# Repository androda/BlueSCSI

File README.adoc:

# F4 BlueSCSI
:toc: macro

`F4 BlueSCSI`, ported by https://github.com/androda[androda], is a fork of `BlueSCSI` which targets the STM32F401 and STM32F411 microcontrollers.

toc::[]

### Lineage
F4 BlueSCSI, BlueSCSI, and ArdSCSino are hardware that reproduces SCSI devices (hard disks) with an STM32 Microcontroller.

`BlueSCSI` was created by https://github.com/erichelgeson[erichelgeson]

`ArdSCSino-stm32` was created by https://github.com/ztto/ArdSCSino-stm32[ztto], and is the STM32 version of `ArdSCSino`

`ArdSCSino` was created by https://twitter.com/h_koma2[Tambo (TNB Seisakusho)]

## Discussion
Join us in #bluescsi on https://discord.gg/GKcvtgU7P9[Discord].

## Compatibility and Performance
https://github.com/androda/F4_BlueSCSI/wiki/System-Compatibility-and-Performance[Compatibility and Performance]

## Assembly
Assembly instructions are generally found on my separate site, here: https://androda.work/kit-assembly/
These aren't really assembly instructions either, mostly pictures of the assembled design with tips on which way things should be facing.

## Usage
https://github.com/erichelgeson/BlueSCSI/wiki/Usage[Usage] is intended to be the same as the parent project and will be kept in sync until the blue pill module's flash is all used.  Then F4 will start to diverge.

### Termination
Termination enable / disable is handled differently per board style.  See the instructions for each PCB design.

## Firmware Updates
https://github.com/androda/F4_BlueSCSI/wiki/Flashing-Firmware-Updates[Flashing Firmware Updates]

## Troubleshooting
(to be completed, currently similar to the parent repo - but there are no jumpers on these dev modules.)
https://github.com/erichelgeson/BlueSCSI/wiki/Troubleshooting

## Hardware Versions
Generally speaking, hardware versions follow a naming scheme.

Variant.Maker.Style.Version

For example: {F4.TbA.D.V1}

This is an F4 model from Tech by Androda, D is for Desktop and V1 means first revision.

## Development (Advanced, annoying to set up)
https://github.com/androda/F4_BlueSCSI/tree/main/docs/Dev_Instructions[Dev Instructions]

## Notes

### Building the Code
- Build experience is unfortunately complex due to Maple's STM32F4 compatibility issues

### Making Gerbers for JLCPCB
https://support.jlcpcb.com/article/44-how-to-export-kicad-pcb-to-gerber-files

BlueSCSI(TM) - Eric Helgeson - All rights reserved. - Used with permission

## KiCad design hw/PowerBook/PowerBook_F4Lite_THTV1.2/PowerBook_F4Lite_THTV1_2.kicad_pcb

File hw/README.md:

# F4 and F4Lite Hardware License

* © 2021 - 2022 Tech by Androda, LLC
* All hardware design files, design artifacts, and in general all files provided in the hardware section (/hw/ and below) are licensed Attribution-NonCommercial-ShareAlike 4.0 International (CC BY-NC-SA 4.0)
* https://creativecommons.org/licenses/by-nc-sa/4.0/legalcode

These files are provided AS-IS with no warranty of any kind to the maximum extent allowed by law.

License Explanation:

Hardware:
This license means that you can have these designs produced by the PCB maker of your choice, for your own personal use.
You, the licensee, are not permitted to re-sell the PCBs which are produced using these design and production files.  They are not licensed for sale of any kind, regardless of whether you have 'spares' left over.  Selling them 'at cost' or 'below cost' is also a violation of the license, because those are sales too.

3D Printable Files:
This license allows you to print these printable files yourself, or have them printed for you, for your own personal use.  You, the licensee, are not permitted to re-sell the printed parts which are produced under this license.  They are not licensed for sale of any kind, regardless of whether you made (or had made) more than you needed.  A sale 'at cost' or 'below cost' is still a sale and is a license violation.

All other files:
Seriously, why would you try to sell these?

Alternate Licensing available:
If you would like to produce these hardware designs and printed parts for sale, you are encouraged to contact Tech by Androda, LLC to arrange alternate licensing.  https://androda.work/about/

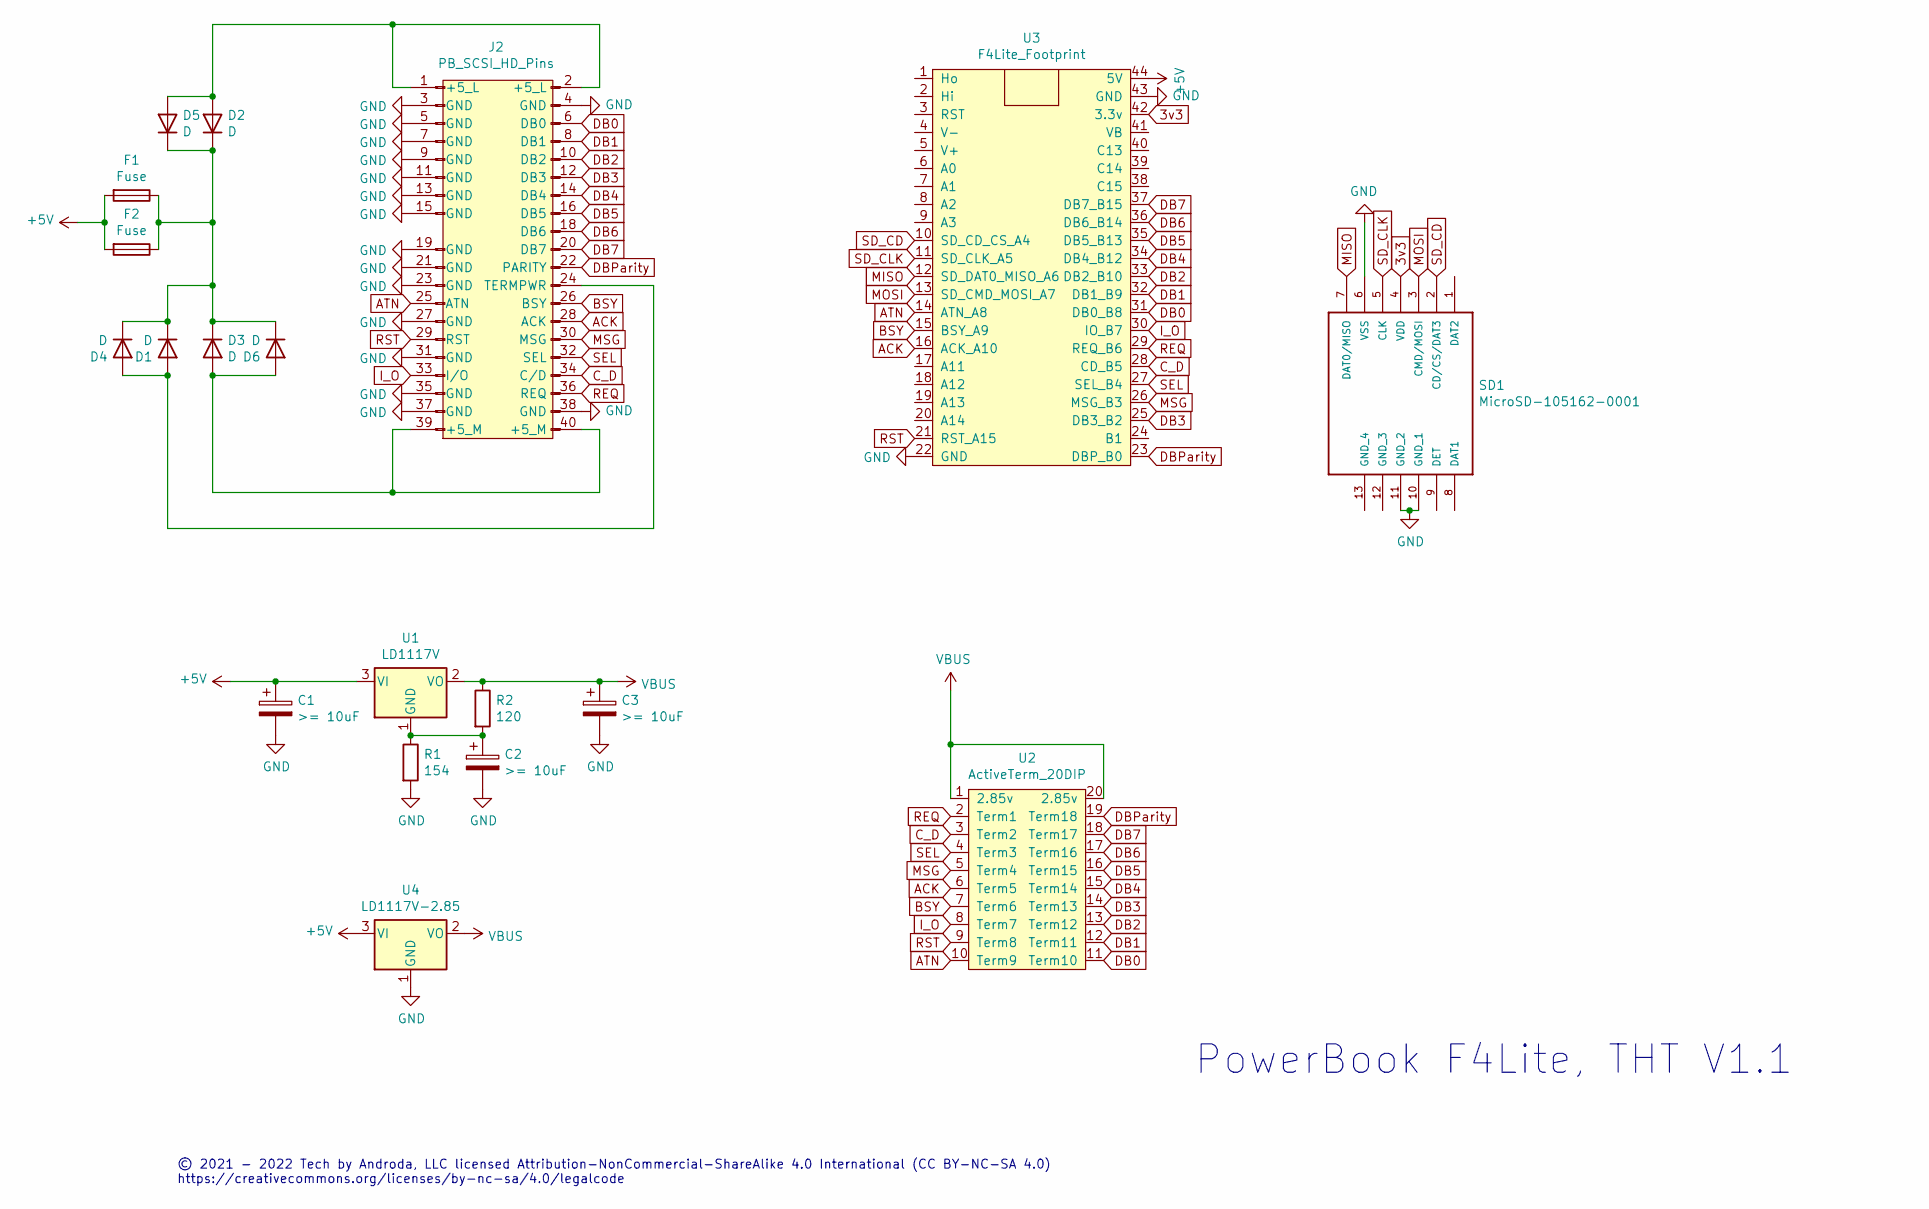
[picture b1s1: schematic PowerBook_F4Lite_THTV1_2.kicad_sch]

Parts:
C1, C2, C3: >= 10uF; C_1206_3216Metric_Pad1.42x1.75mm_HandSolder
D1, D2, D3: D; D_A-405_P10.16mm_Horizontal
D4, D5, D6: D; D_SMA
F1: Fuse; Fuse_BelFuse_0ZRE0005FF_L8.3mm_W3.8mm
F2: Fuse; Fuse_0805_2012Metric_Pad1.15x1.40mm_HandSolder
J2: PB_SCSI_HD_Pins; PowerBook_SCSI_40Pin_UpsideDown
R1: 154; R_Axial_DIN0204_L3.6mm_D1.6mm_P7.62mm_Horizontal
R2: 120; R_Axial_DIN0204_L3.6mm_D1.6mm_P5.08mm_Vertical
SD1: MicroSD-105162-0001; microsd_molex_1051620001; MANUFACTURER_PART_NUMBER 105162-0001; MOUSER_PART_NUMBER 538-105162-0001
U1: LD1117V; TO-220-3_Horizontal_TabDown
U2: ActiveTerm_20DIP; DIP-20_W7.62mm_Socket
U3: F4Lite_Footprint
U4: LD1117V-2.85; SOT-223-3_TabPin2

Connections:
3v3: SD1.4 (VDD), U3.42 (3.3v)
+5V: C1.1, F1.2, F2.2, U1.3 (VI), U3.44 (5V), U4.3 (VI)
ACK: J2.28 (ACK), U2.6 (Term5), U3.16 (ACK_A10)
ATN: J2.25 (ATN), U2.10 (Term9), U3.14 (ATN_A8)
BSY: J2.26 (BSY), U2.7 (Term6), U3.15 (BSY_A9)
C_D: J2.34 (C/D), U2.3 (Term2), U3.28 (CD_B5)
DB0: J2.6 (DB0), U2.11 (Term10), U3.31 (DB0_B8)
DB1: J2.8 (DB1), U2.12 (Term11), U3.32 (DB1_B9)
DB2: J2.10 (DB2), U2.13 (Term12), U3.33 (DB2_B10)
DB3: J2.12 (DB3), U2.14 (Term13), U3.25 (DB3_B2)
DB4: J2.14 (DB4), U2.15 (Term14), U3.34 (DB4_B12)
DB5: J2.16 (DB5), U2.16 (Term15), U3.35 (DB5_B13)
DB6: J2.18 (DB6), U2.17 (Term16), U3.36 (DB6_B14)
DB7: J2.20 (DB7), U2.18 (Term17), U3.37 (DB7_B15)
DBParity: J2.22 (PARITY), U2.19 (Term18), U3.23 (DBP_B0)
GND: C1.2, C2.2, C3.2, J2.3 (GND), J2.4 (GND), J2.5 (GND), J2.7 (GND), J2.9 (GND), J2.11 (GND), J2.13 (GND), J2.15 (GND), J2.19 (GND), J2.21 (GND), J2.23 (GND), J2.27 (GND), J2.31 (GND), J2.35 (GND), J2.37 (GND), J2.38 (GND), R1.2, SD1.6 (VSS), SD1.10 (GND_1), SD1.11 (GND_2), U3.22 (GND), U3.43 (GND), U4.1 (GND)
I_O: J2.33 (I/O), U2.8 (Term7), U3.30 (IO_B7)
MISO: SD1.7 (DAT0/MISO), U3.12 (SD_DAT0_MISO_A6)
MOSI: SD1.3 (CMD/MOSI), U3.13 (SD_CMD_MOSI_A7)
MSG: J2.30 (MSG), U2.5 (Term4), U3.26 (MSG_B3)
unnamed: C2.1, R1.1, R2.2, U1.1 (GND)
unnamed: D1.1 (K), D2.1 (K), D3.1 (K), D4.1 (K), D5.1 (K), D6.1 (K), F1.1, F2.1
unnamed: D1.2 (A), D4.2 (A), J2.24 (TERMPWR)
unnamed: D2.2 (A), D5.2 (A), J2.1 (+5_L), J2.2 (+5_L)
unnamed: D3.2 (A), D6.2 (A), J2.39 (+5_M), J2.40 (+5_M)
REQ: J2.36 (REQ), U2.2 (Term1), U3.29 (REQ_B6)
RST: J2.29 (RST), U2.9 (Term8), U3.21 (RST_A15)
SD_CD: SD1.2 (CD/CS/DAT3), U3.10 (SD_CD_CS_A4)
SD_CLK: SD1.5 (CLK), U3.11 (SD_CLK_A5)
SEL: J2.32 (SEL), U2.4 (Term3), U3.27 (SEL_B4)
VBUS: C3.1, R2.1, U1.2 (VO), U2.1 (2.85v), U2.20 (2.85v), U4.2 (VO)

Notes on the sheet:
© 2021 - 2022 Tech by Androda, LLC licensed Attribution-NonCommercial-ShareAlike 4.0 International (CC BY-NC-SA 4.0) https://creativecommons.org/licenses/by-nc-sa/4.0/legalcode
PowerBook F4Lite, THT V1.1

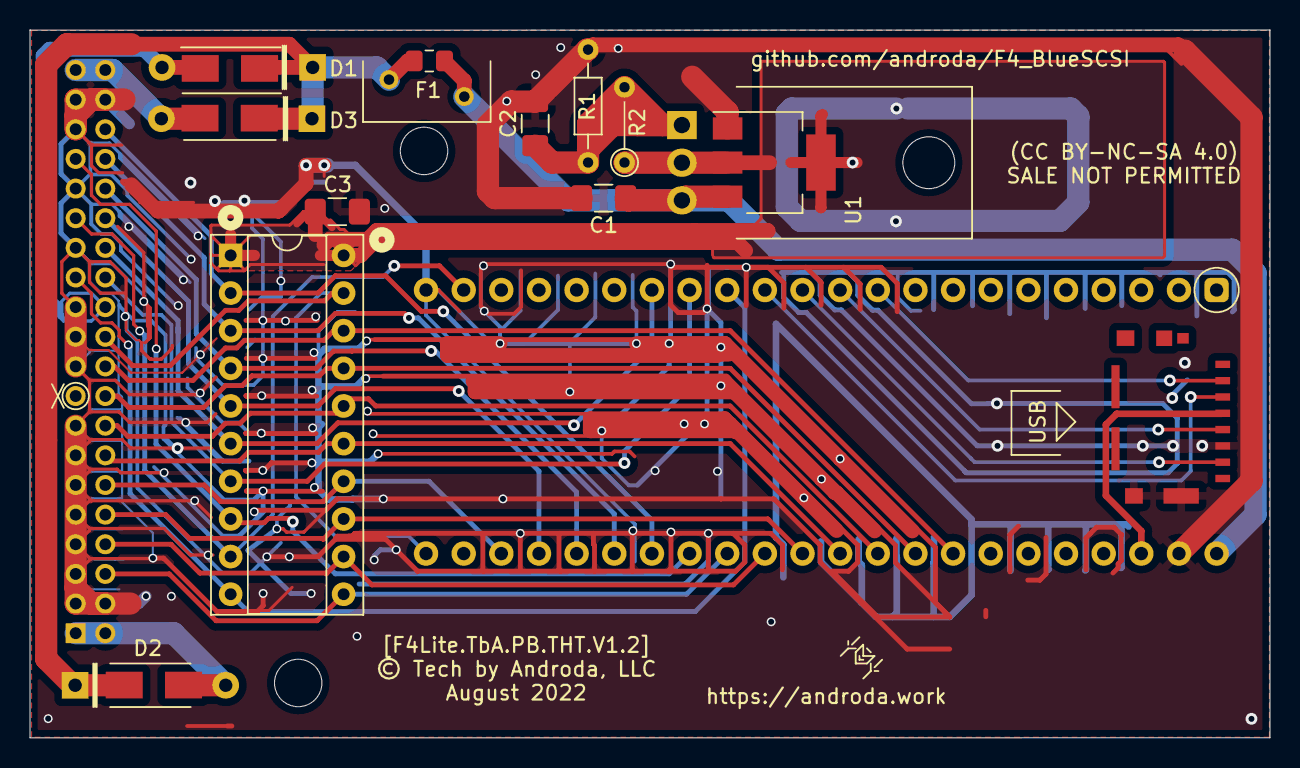
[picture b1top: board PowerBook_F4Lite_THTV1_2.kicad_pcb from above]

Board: 2 copper layers, 83.7 x 47.8 mm, 19 parts (0 on the bottom side), 31 nets.

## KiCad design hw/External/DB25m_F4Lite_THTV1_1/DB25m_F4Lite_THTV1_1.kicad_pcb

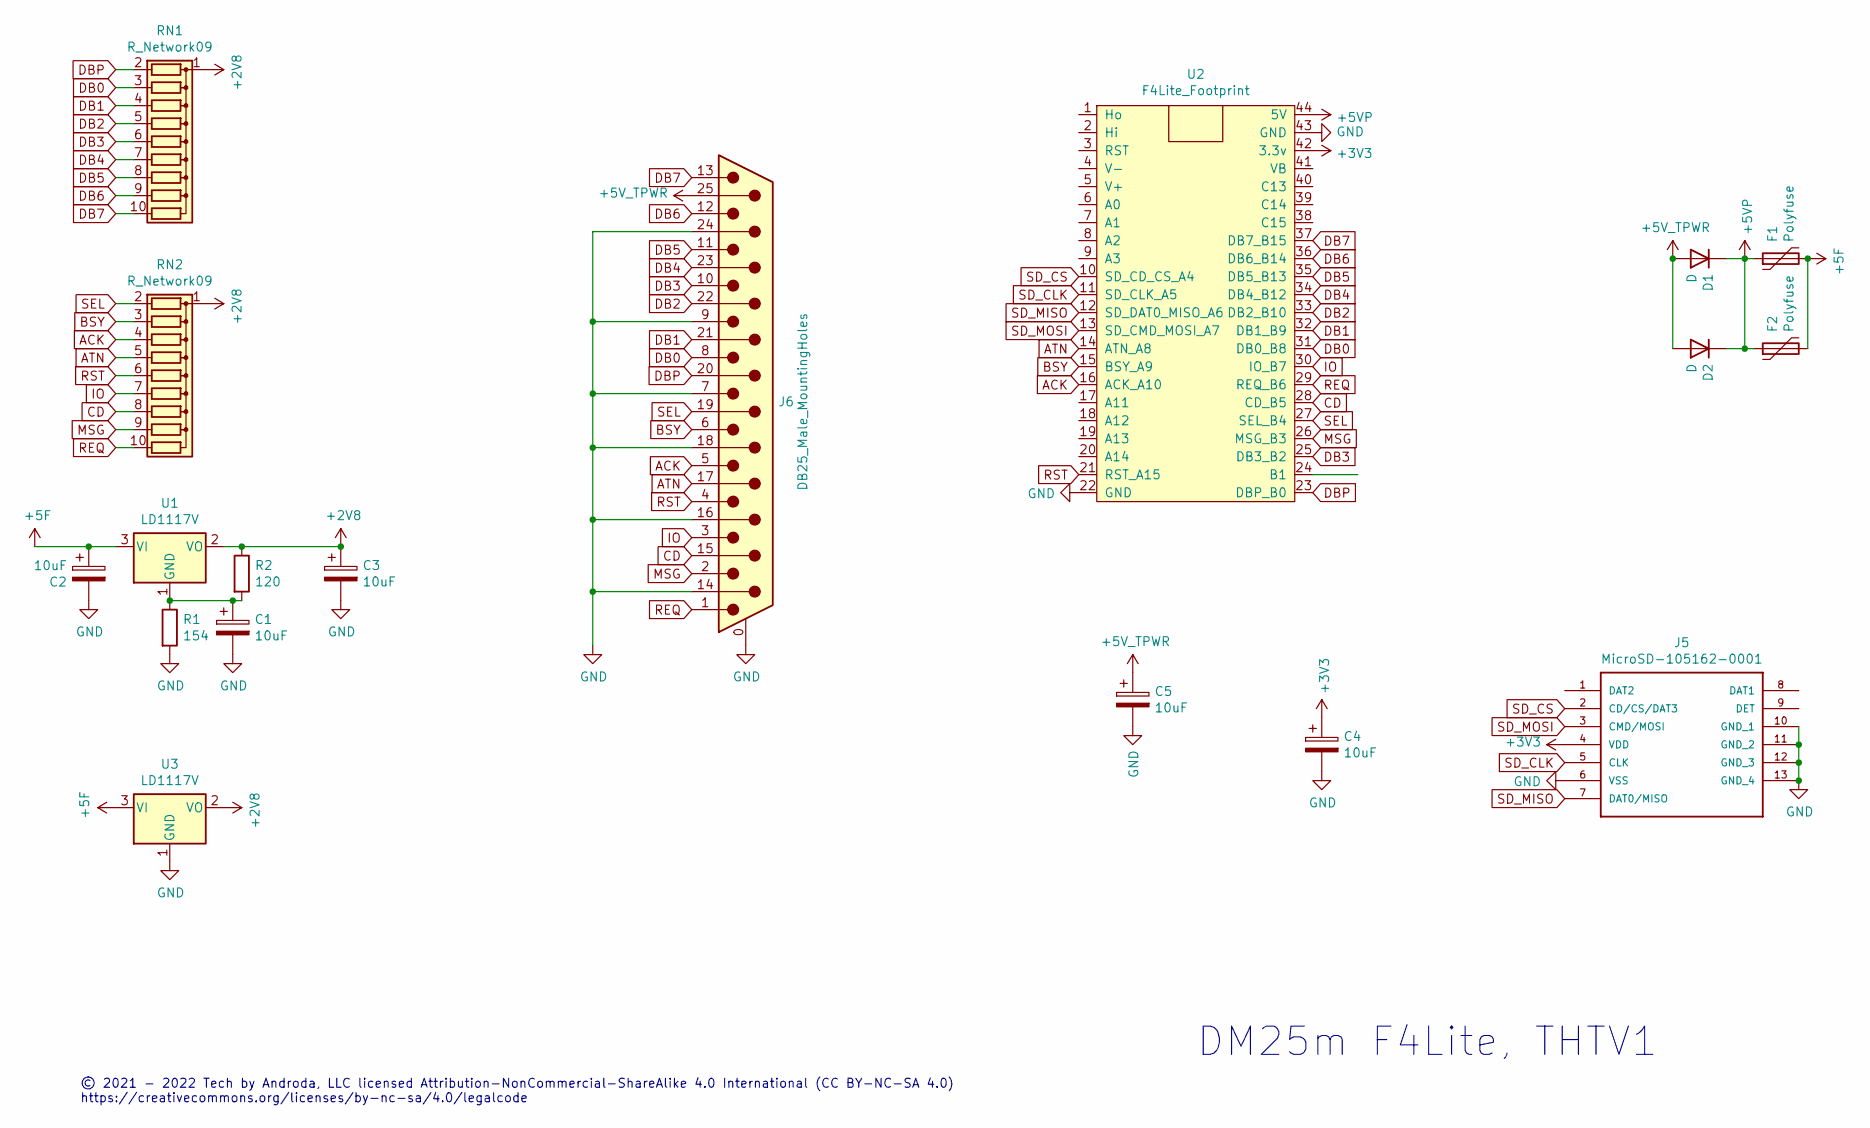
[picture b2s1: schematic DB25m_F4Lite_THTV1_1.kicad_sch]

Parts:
C1, C2, C3, C4: 10uF; C_1210_3225Metric_Pad1.42x2.65mm_HandSolder
C5: 10uF; C_0805_2012Metric_Pad1.18x1.45mm_HandSolder
D1: D; D_A-405_P10.16mm_Horizontal
D2: D; D_SMA
F1: Polyfuse; Fuse_BelFuse_0ZRE0005FF_L8.3mm_W3.8mm
F2: Polyfuse; Fuse_0805_2012Metric_Pad1.15x1.40mm_HandSolder
J5: MicroSD-105162-0001; microsd_molex_1051620001; MANUFACTURER_PART_NUMBER 105162-0001; MOUSER_PART_NUMBER 538-105162-0001
J6: DB25_Male_MountingHoles; DSUB-25_Male_Horizontal_P2.77x2.84mm_EdgePinOffset7.70mm_Ho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
R1: 154; R_Axial_DIN0207_L6.3mm_D2.5mm_P10.16mm_Horizontal
R2: 120; R_Axial_DIN0204_L3.6mm_D1.6mm_P5.08mm_Vertical
RN1, RN2: R_Network09; R_Array_SIP10
U1: LD1117V; TO-220-3_Horizontal_TabDown
U2: F4Lite_Footprint
U3: LD1117V; SOT-223-3_TabPin2

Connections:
+2V8: C3.1, R2.1, RN1.1 (common), RN2.1 (common), U1.2 (VO), U3.2 (VO)
+3V3: C4.1, J5.4 (VDD), U2.42 (3.3v)
+5F: C2.1, F1.2, F2.2, U1.3 (VI), U3.3 (VI)
+5V: C5.1, D1.2 (A), D2.2 (A), J6.25
+5VP: D1.1 (K), D2.1 (K), F1.1, F2.1, U2.44 (5V)
ACK: J6.5, RN2.4 (R3), U2.16 (ACK_A10)
ATN: J6.17, RN2.5 (R4), U2.14 (ATN_A8)
BSY: J6.6, RN2.3 (R2), U2.15 (BSY_A9)
CD: J6.15, RN2.8 (R7), U2.28 (CD_B5)
DB0: J6.8, RN1.3 (R2), U2.31 (DB0_B8)
DB1: J6.21, RN1.4 (R3), U2.32 (DB1_B9)
DB2: J6.22, RN1.5 (R4), U2.33 (DB2_B10)
DB3: J6.10, RN1.6 (R5), U2.25 (DB3_B2)
DB4: J6.23, RN1.7 (R6), U2.34 (DB4_B12)
DB5: J6.11, RN1.8 (R7), U2.35 (DB5_B13)
DB6: J6.12, RN1.9 (R8), U2.36 (DB6_B14)
DB7: J6.13, RN1.10 (R9), U2.37 (DB7_B15)
DBP: J6.20, RN1.2 (R1), U2.23 (DBP_B0)
GND: C1.2, C2.2, C3.2, C4.2, C5.2, J5.6 (VSS), J5.10 (GND_1), J5.11 (GND_2), J5.12 (GND_3), J5.13 (GND_4), J6.0 (PAD), J6.7, J6.9, J6.14, J6.16, J6.18, J6.24, R1.2, U2.22 (GND), U2.43 (GND), U3.1 (GND)
IO: J6.3, RN2.7 (R6), U2.30 (IO_B7)
MSG: J6.2, RN2.9 (R8), U2.26 (MSG_B3)
unnamed: C1.1, R1.1, R2.2, U1.1 (GND)
REQ: J6.1, RN2.10 (R9), U2.29 (REQ_B6)
RST: J6.4, RN2.6 (R5), U2.21 (RST_A15)
SD_CLK: J5.5 (CLK), U2.11 (SD_CLK_A5)
SD_CS: J5.2 (CD/CS/DAT3), U2.10 (SD_CD_CS_A4)
SD_MISO: J5.7 (DAT0/MISO), U2.12 (SD_DAT0_MISO_A6)
SD_MOSI: J5.3 (CMD/MOSI), U2.13 (SD_CMD_MOSI_A7)
SEL: J6.19, RN2.2 (R1), U2.27 (SEL_B4)

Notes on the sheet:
© 2021 - 2022 Tech by Androda, LLC licensed Attribution-NonCommercial-ShareAlike 4.0 International (CC BY-NC-SA 4.0) https://creativecommons.org/licenses/by-nc-sa/4.0/legalcode
DM25m F4Lite, THTV1

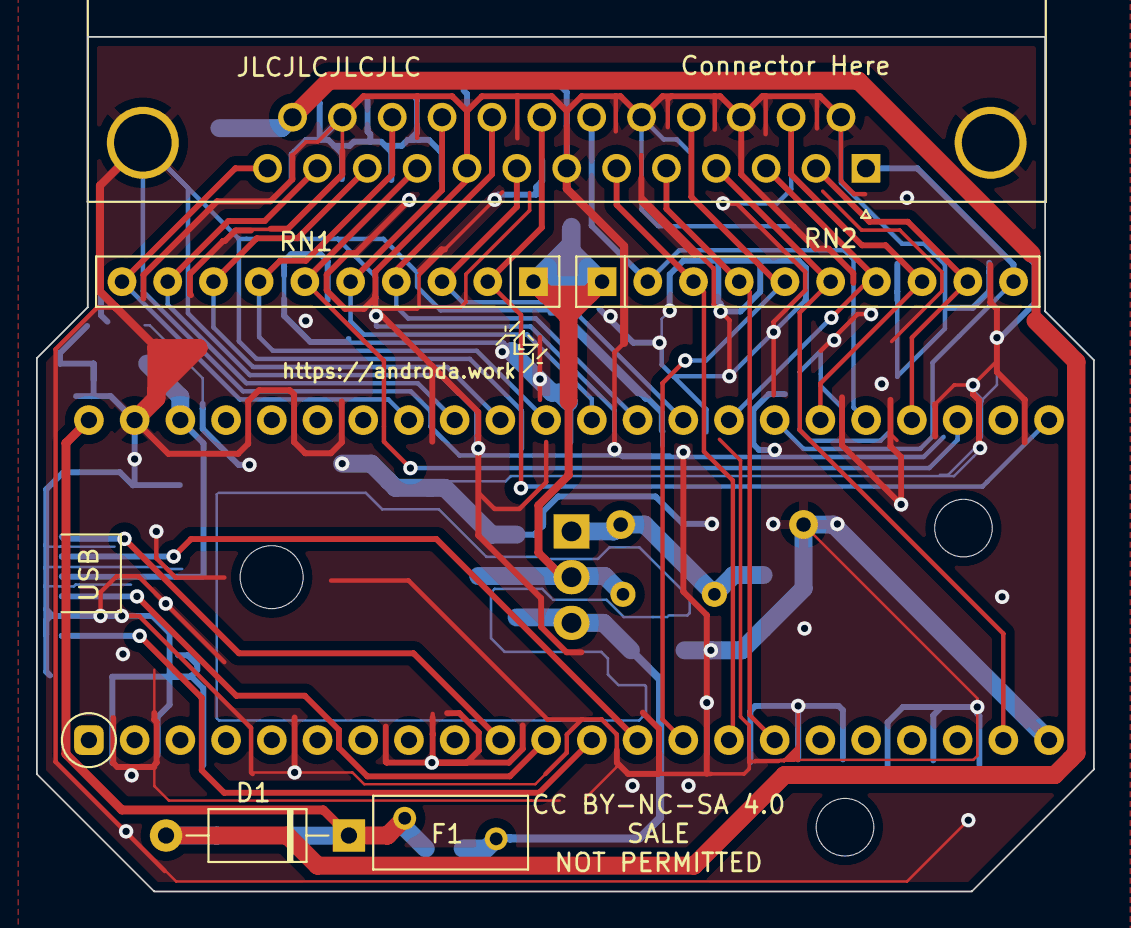
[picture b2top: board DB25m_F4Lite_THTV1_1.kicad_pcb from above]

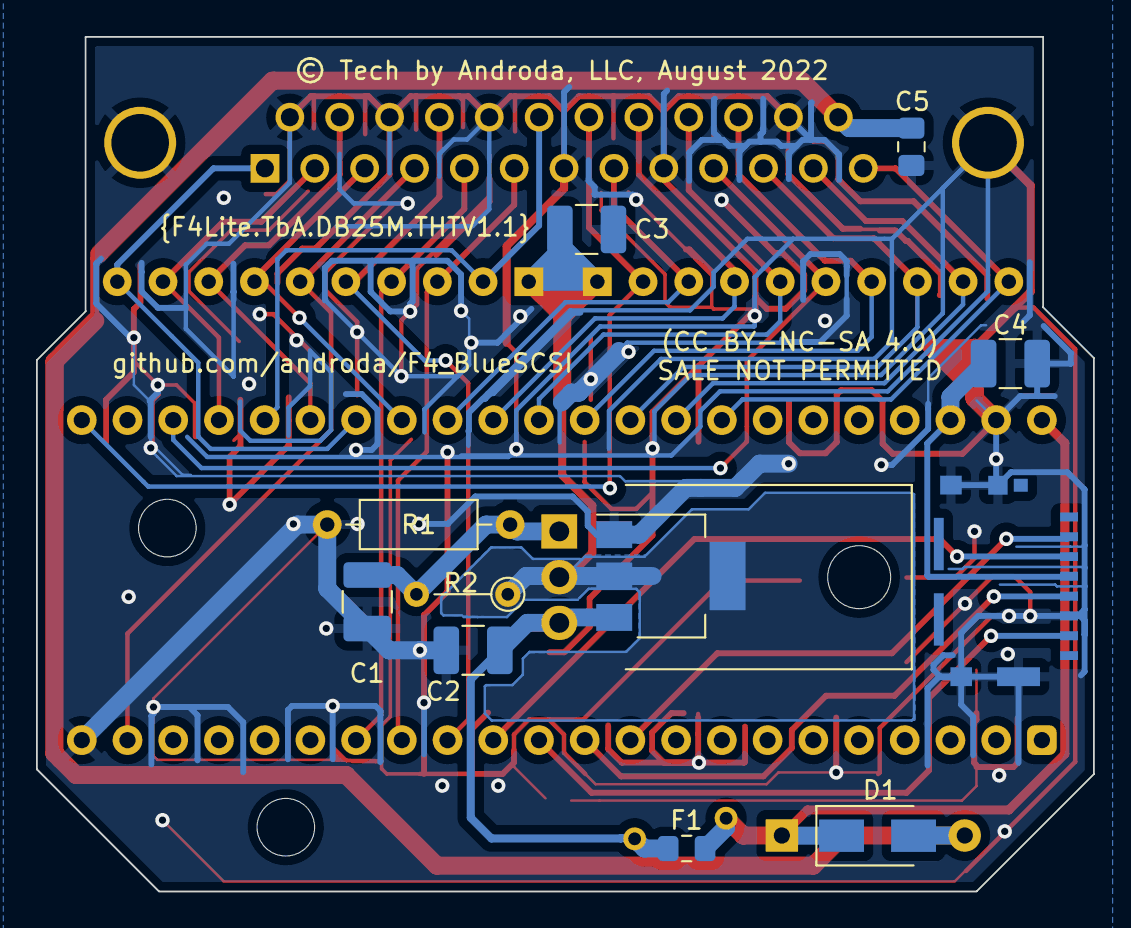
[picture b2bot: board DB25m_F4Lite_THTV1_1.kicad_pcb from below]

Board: 2 copper layers, 58.7 x 47.5 mm, 18 parts (12 on the bottom side), 29 nets.

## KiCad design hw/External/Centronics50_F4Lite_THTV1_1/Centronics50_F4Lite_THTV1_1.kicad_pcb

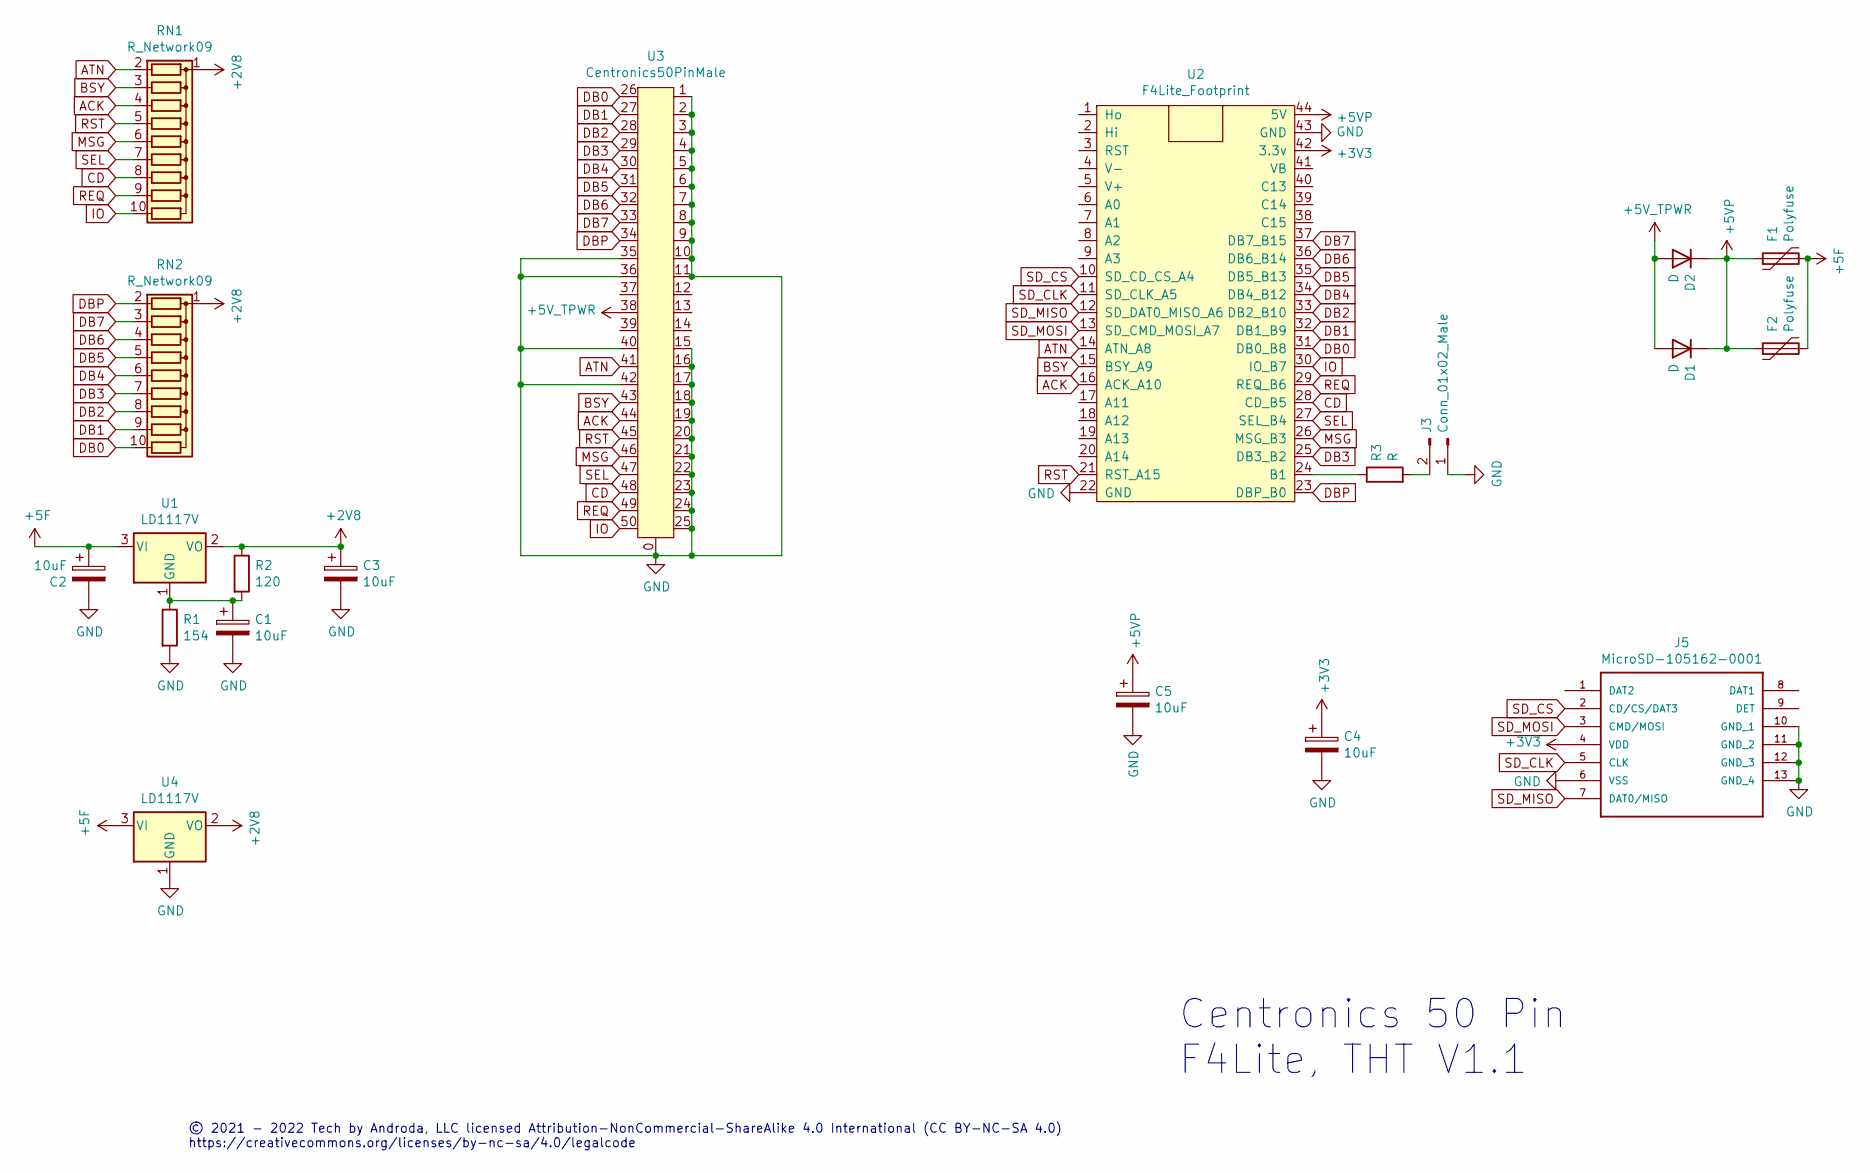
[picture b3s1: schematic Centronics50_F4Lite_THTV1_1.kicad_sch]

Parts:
C1, C2, C3, C4: 10uF; C_1210_3225Metric_Pad1.42x2.65mm_HandSolder
C5: 10uF; C_0805_2012Metric_Pad1.18x1.45mm_HandSolder
D1: D; D_SMA
D2: D; D_A-405_P10.16mm_Horizontal
F1: Polyfuse; Fuse_BelFuse_0ZRE0005FF_L8.3mm_W3.8mm
F2: Polyfuse; Fuse_0805_2012Metric_Pad1.15x1.40mm_HandSolder
J3: Conn_01x02_Male; PinHeader_1x02_P2.54mm_Vertical
J5: MicroSD-105162-0001; microsd_molex_1051620001; MANUFACTURER_PART_NUMBER 105162-0001; MOUSER_PART_NUMBER 538-105162-0001
R1: 154; R_Axial_DIN0207_L6.3mm_D2.5mm_P10.16mm_Horizontal
R2: 120; R_Axial_DIN0204_L3.6mm_D1.6mm_P5.08mm_Vertical
R3: R; R_Axial_DIN0207_L6.3mm_D2.5mm_P7.62mm_Horizontal
RN1, RN2: R_Network09; R_Array_SIP10
U1: LD1117V; TO-220-3_Horizontal_TabDown
U2: F4Lite_Footprint
U3: Centronics50PinMale; Centronics50Male
U4: LD1117V; SOT-223-3_TabPin2

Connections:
+2V8: C3.1, R2.1, RN1.1 (common), RN2.1 (common), U1.2 (VO), U4.2 (VO)
+3V3: C4.1, J5.4 (VDD), U2.42 (3.3v)
+5F: C2.1, F1.2, F2.2, U1.3 (VI), U4.3 (VI)
+5V: D1.2 (A), D2.2 (A), U3.38
+5VP: C5.1, D1.1 (K), D2.1 (K), F1.1, F2.1, U2.44 (5V)
ACK: RN1.4 (R3), U2.16 (ACK_A10), U3.44
ATN: RN1.2 (R1), U2.14 (ATN_A8), U3.41
BSY: RN1.3 (R2), U2.15 (BSY_A9), U3.43
CD: RN1.8 (R7), U2.28 (CD_B5), U3.48
DB0: RN2.10 (R9), U2.31 (DB0_B8), U3.26
DB1: RN2.9 (R8), U2.32 (DB1_B9), U3.27
DB2: RN2.8 (R7), U2.33 (DB2_B10), U3.28
DB3: RN2.7 (R6), U2.25 (DB3_B2), U3.29
DB4: RN2.6 (R5), U2.34 (DB4_B12), U3.30
DB5: RN2.5 (R4), U2.35 (DB5_B13), U3.31
DB6: RN2.4 (R3), U2.36 (DB6_B14), U3.32
DB7: RN2.3 (R2), U2.37 (DB7_B15), U3.33
DBP: RN2.2 (R1), U2.23 (DBP_B0), U3.34
GND: C1.2, C2.2, C3.2, C4.2, C5.2, J3.1, J5.6 (VSS), J5.10 (GND_1), J5.11 (GND_2), J5.12 (GND_3), J5.13 (GND_4), R1.2, U2.22 (GND), U2.43 (GND), U3.0, U3.1, U3.2, U3.3, U3.4, U3.5, U3.6, U3.7, U3.8, U3.9, U3.10, U3.11, U3.15, U3.16, U3.17, U3.18, U3.19, U3.20, U3.21, U3.22, U3.23, U3.24, U3.25, U3.35, U3.36, U3.40, U3.42, U4.1 (GND)
IO: RN1.10 (R9), U2.30 (IO_B7), U3.50
MSG: RN1.6 (R5), U2.26 (MSG_B3), U3.46
unnamed: C1.1, R1.1, R2.2, U1.1 (GND)
unnamed: J3.2, R3.2
unnamed: R3.1, U2.24 (B1)
REQ: RN1.9 (R8), U2.29 (REQ_B6), U3.49
RST: RN1.5 (R4), U2.21 (RST_A15), U3.45
SD_CLK: J5.5 (CLK), U2.11 (SD_CLK_A5)
SD_CS: J5.2 (CD/CS/DAT3), U2.10 (SD_CD_CS_A4)
SD_MISO: J5.7 (DAT0/MISO), U2.12 (SD_DAT0_MISO_A6)
SD_MOSI: J5.3 (CMD/MOSI), U2.13 (SD_CMD_MOSI_A7)
SEL: RN1.7 (R6), U2.27 (SEL_B4), U3.47

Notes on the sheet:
Centronics 50 Pin F4Lite, THT V1.1
© 2021 - 2022 Tech by Androda, LLC licensed Attribution-NonCommercial-ShareAlike 4.0 International (CC BY-NC-SA 4.0) https://creativecommons.org/licenses/by-nc-sa/4.0/legalcode

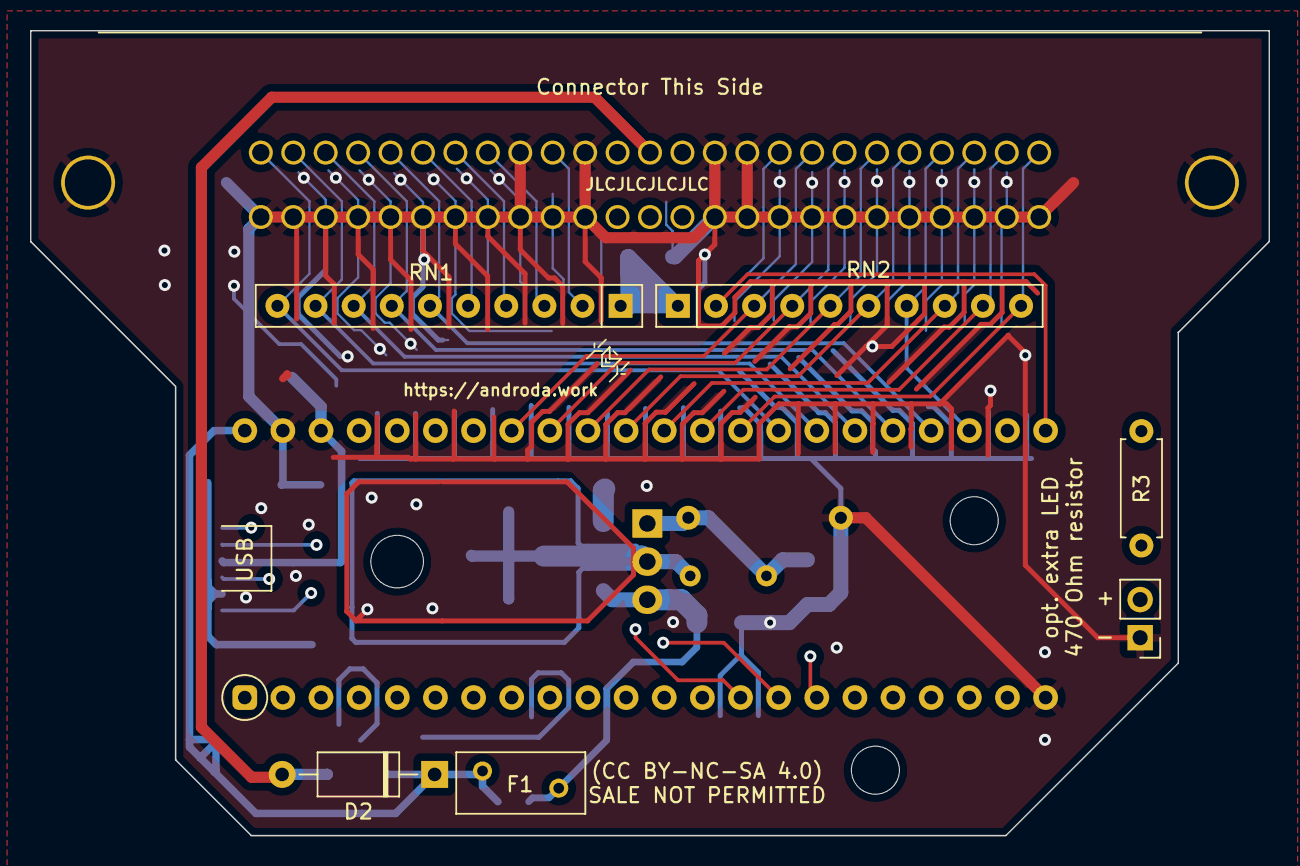
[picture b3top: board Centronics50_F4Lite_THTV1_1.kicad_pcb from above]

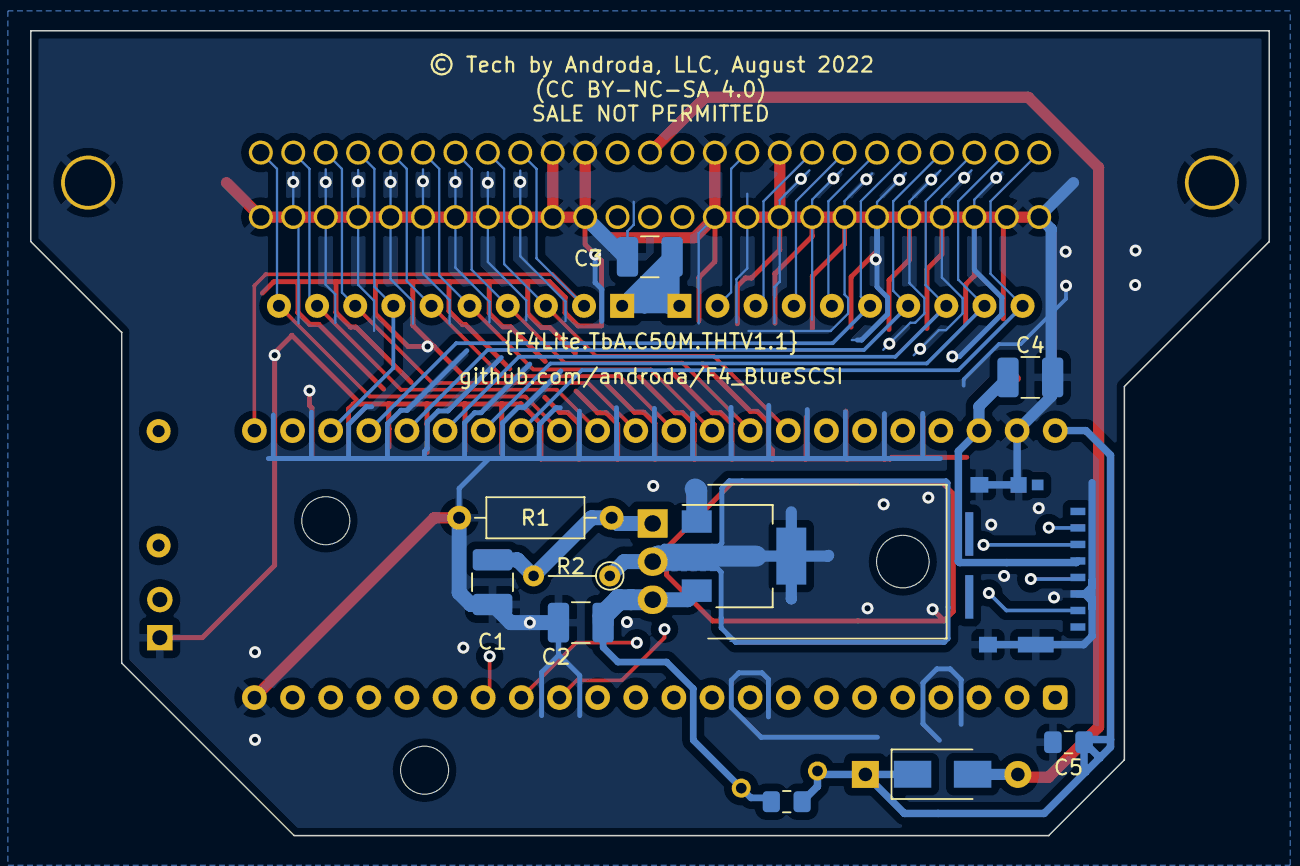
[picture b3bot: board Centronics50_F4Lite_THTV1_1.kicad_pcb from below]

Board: 4 copper layers, 82.5 x 53.6 mm, 20 parts (12 on the bottom side), 31 nets.

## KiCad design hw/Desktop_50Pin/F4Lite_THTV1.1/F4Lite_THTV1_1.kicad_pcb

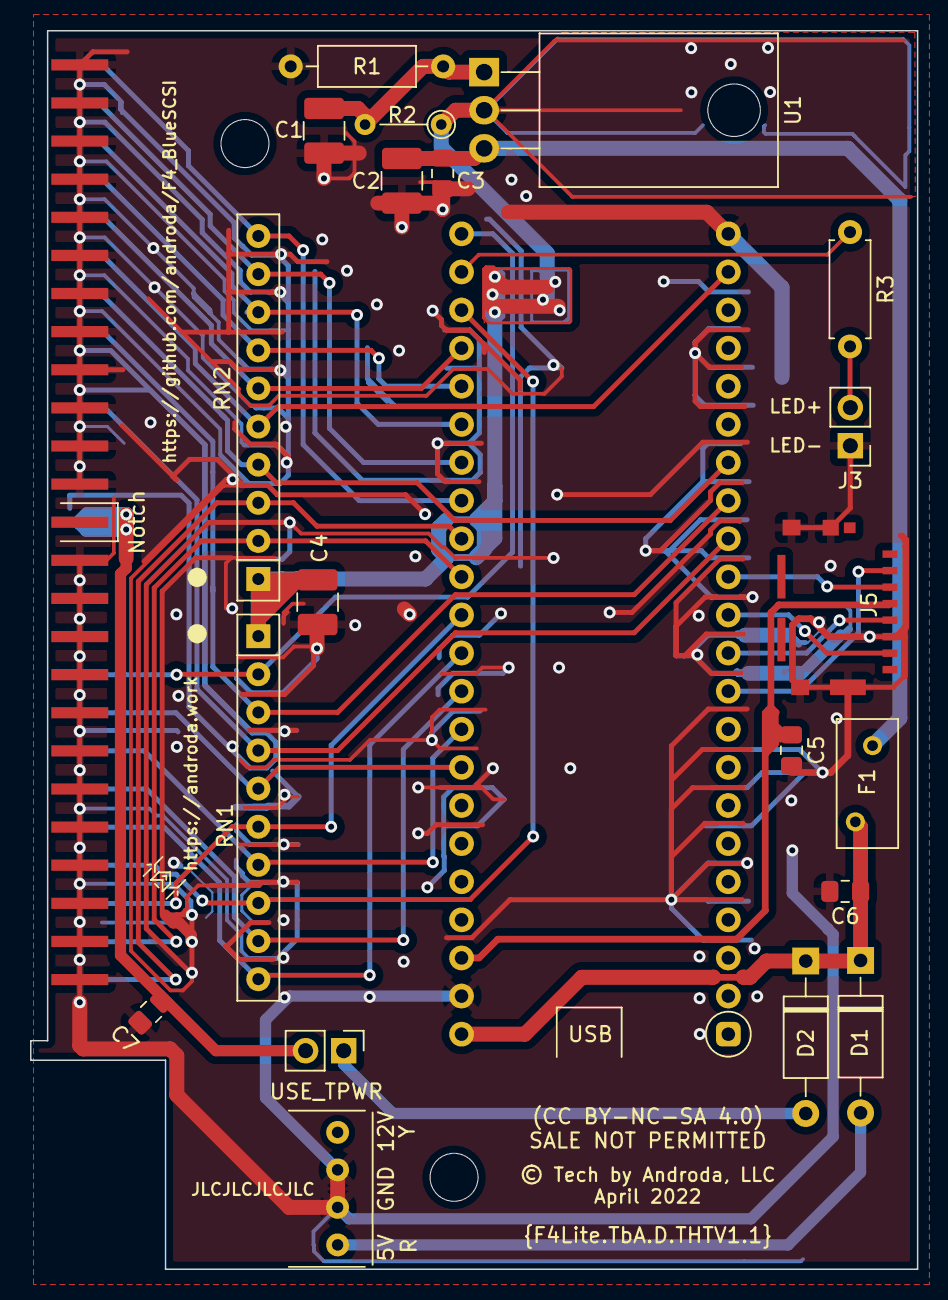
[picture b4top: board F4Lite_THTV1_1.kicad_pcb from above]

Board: 2 copper layers, 59.1 x 82.5 mm, 22 parts (0 on the bottom side), 33 nets.

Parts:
C1, C2, C4: 10uF; C_1210_3225Metric_Pad1.42x2.65mm_HandSolder
C3: 0.1uF; C_0805_2012Metric_Pad1.15x1.40mm_HandSolder
C5, C6, C7: 4.7uF; C_0805_2012Metric_Pad1.15x1.40mm_HandSolder
D1, D2: D; D_A-405_P10.16mm_Horizontal
F1: Polyfuse; Fuse_BelFuse_0ZRE0005FF_L8.3mm_W3.8mm
J1, J3: Conn_01x02_Male; PinHeader_1x02_P2.54mm_Vertical
J2: BergFloppy; BergFloppy_RightAngle
J4: SCSI_50Pin; SCSI50_EdgeConn
J5: MicroSD-105162-0001; microsd_molex_1051620001
R1: 154; R_Axial_DIN0207_L6.3mm_D2.5mm_P10.16mm_Horizontal
R2: 120; R_Axial_DIN0204_L3.6mm_D1.6mm_P5.08mm_Vertical
R3: R; R_Axial_DIN0207_L6.3mm_D2.5mm_P7.62mm_Horizontal
RN1, RN2: R_Network09; R_Array_SIP10
U1: AMS1117CD-2.85; TO-220-3_Horizontal_TabDown
U2: GreenSCSI_F401

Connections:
+2V8: C4.1, R2.1, RN1.1, RN2.1, U1.2
+3V3: C5.1, J5.4, U2.42
+5F: C2.1, C3.1, F1.2, U1.3
+5V: C7.1, J1.2, J4.26
+5VP: C6.1, D1.1, D2.1, F1.1, U2.44
ACK: J4.38, RN2.4, U2.16
ATN: J4.32, RN1.4, U2.14
BSY: J4.36, RN1.3, U2.15
CD: J4.46, RN2.8, U2.28
DB0: J4.2, RN2.3, U2.31
DB1: J4.4, RN2.2, U2.32
DB2: J4.6, RN1.6, U2.33
DB3: J4.8, RN1.8, U2.25
DB4: J4.10, RN1.10, U2.34
DB5: J4.12, RN1.9, U2.35
DB6: J4.14, RN1.7, U2.36
DB7: J4.16, RN1.5, U2.37
DBP: J4.18, RN1.2, U2.23
GND: C1.2, C2.2, C3.2, C4.2, C5.2, C6.2, C7.2, J2.2, J2.3, J3.1, J4.1, J4.3, J4.5, J4.7, J4.9, J4.11, J4.13, J4.15, J4.17, J4.19, J4.21, J4.23, J4.27, J4.29, J4.31, J4.33, J4.35, J4.37, J4.39, J4.41, J4.43, J4.45, J4.47, J4.49, J5.6, J5.10, J5.11, J5.12, J5.13, R1.2, U2.22, U2.43
IO: J4.50, RN2.10, U2.30
MSG: J4.42, RN2.6, U2.26
unnamed: C1.1, R1.1, R2.2, U1.1
unnamed: D1.2, J2.1
unnamed: D2.2, J1.1
unnamed: J3.2, R3.2
unnamed: R3.1, U2.24
REQ: J4.48, RN2.9, U2.29
RST: J4.40, RN2.5, U2.21
SD_CLK: J5.5, U2.11
SD_CS: J5.2, U2.10
SD_MISO: J5.7, U2.12
SD_MOSI: J5.3, U2.13
SEL: J4.44, RN2.7, U2.27

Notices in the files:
hw/Desktop_50Pin/F4Lite_THTV1.1/F4Lite_THTV1_1.kicad_pcb:
© Tech by Androda, LLC
hw/External/Centronics50_F4Lite_THTV1_1/Centronics50_F4Lite_THTV1_1.kicad_pcb:
© Tech by Androda, LLC, August 2022
